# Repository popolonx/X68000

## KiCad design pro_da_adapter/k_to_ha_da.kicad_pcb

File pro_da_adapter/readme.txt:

kicad files (including gerber.zip) for adapter to put HA19510 DA into X68000 pro original IR3K07 socket

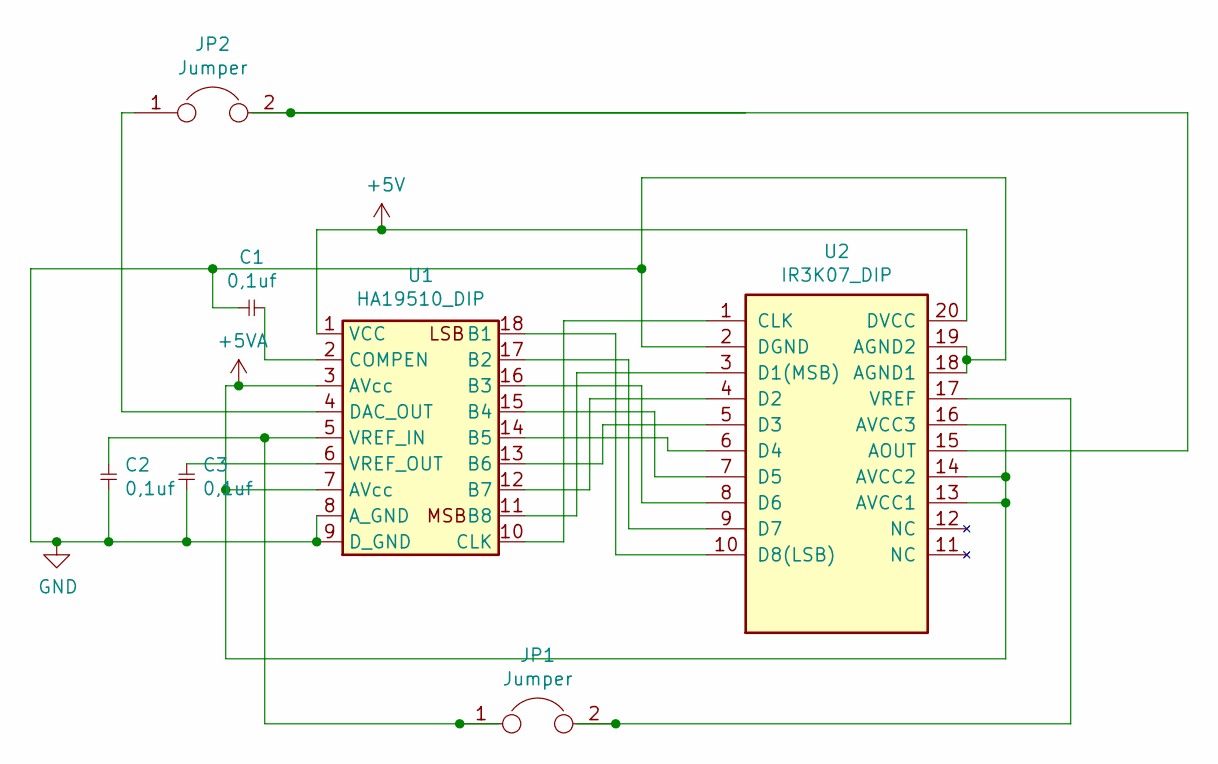
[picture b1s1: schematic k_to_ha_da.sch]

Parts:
C1, C2, C3: 0,1uf; C_Disc_D4.3mm_W1.9mm_P5.00mm
JP1, JP2: Jumper; PinHeader_1x02_P2.54mm_Vertical
U1: HA19510_DIP; DIP-18_W7.62mm
U2: IR3K07_DIP; DIP-20_W7.62mm

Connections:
+5V: U1.1 (VCC), U2.20 (DVCC)
+5VA: U1.3 (AVcc), U1.7 (AVcc), U2.13 (AVCC1), U2.14 (AVCC2), U2.16 (AVCC3)
GND: C1.1, C2.1, C3.1, U1.8 (A_GND), U1.9 (D_GND), U2.2 (DGND), U2.18 (AGND1), U2.19 (AGND2)
unnamed: C1.2, U1.2 (COMPEN)
unnamed: C2.2, JP1.1, U1.5 (VREF_IN)
unnamed: C3.2, U1.6 (VREF_OUT)
unnamed: JP1.2, U2.17 (VREF)
unnamed: JP2.1, U1.4 (DAC_OUT)
unnamed: JP2.2, U2.15 (AOUT)
unnamed: U1.10 (CLK), U2.1 (CLK)
unnamed: U1.11 (B8), U2.3 (D1(MSB))
unnamed: U1.12 (B7), U2.4 (D2)
unnamed: U1.13 (B6), U2.5 (D3)
unnamed: U1.14 (B5), U2.6 (D4)
unnamed: U1.15 (B4), U2.7 (D5)
unnamed: U1.16 (B3), U2.8 (D6)
unnamed: U1.17 (B2), U2.9 (D7)
unnamed: U1.18 (B1), U2.10 (D8(LSB))

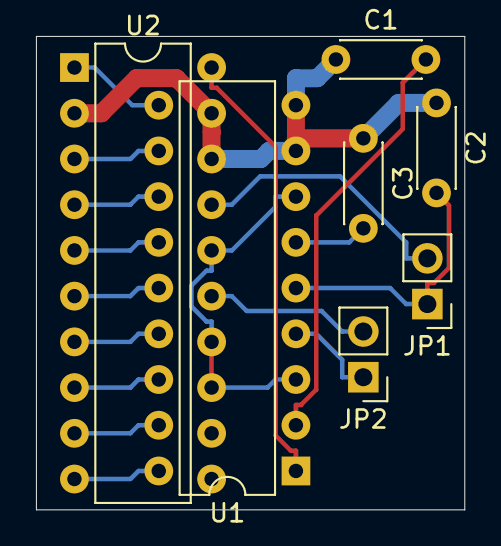
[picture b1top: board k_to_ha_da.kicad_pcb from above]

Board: 2 copper layers, 23.8 x 26.3 mm, 7 parts (0 on the bottom side), 18 nets.
